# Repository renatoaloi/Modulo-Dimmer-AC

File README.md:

# Modulo-Dimmer-AC
Arquivos do EAGLE CAD do Módulo Dimmer AC REV3, incluindo GERBERs para fabricação

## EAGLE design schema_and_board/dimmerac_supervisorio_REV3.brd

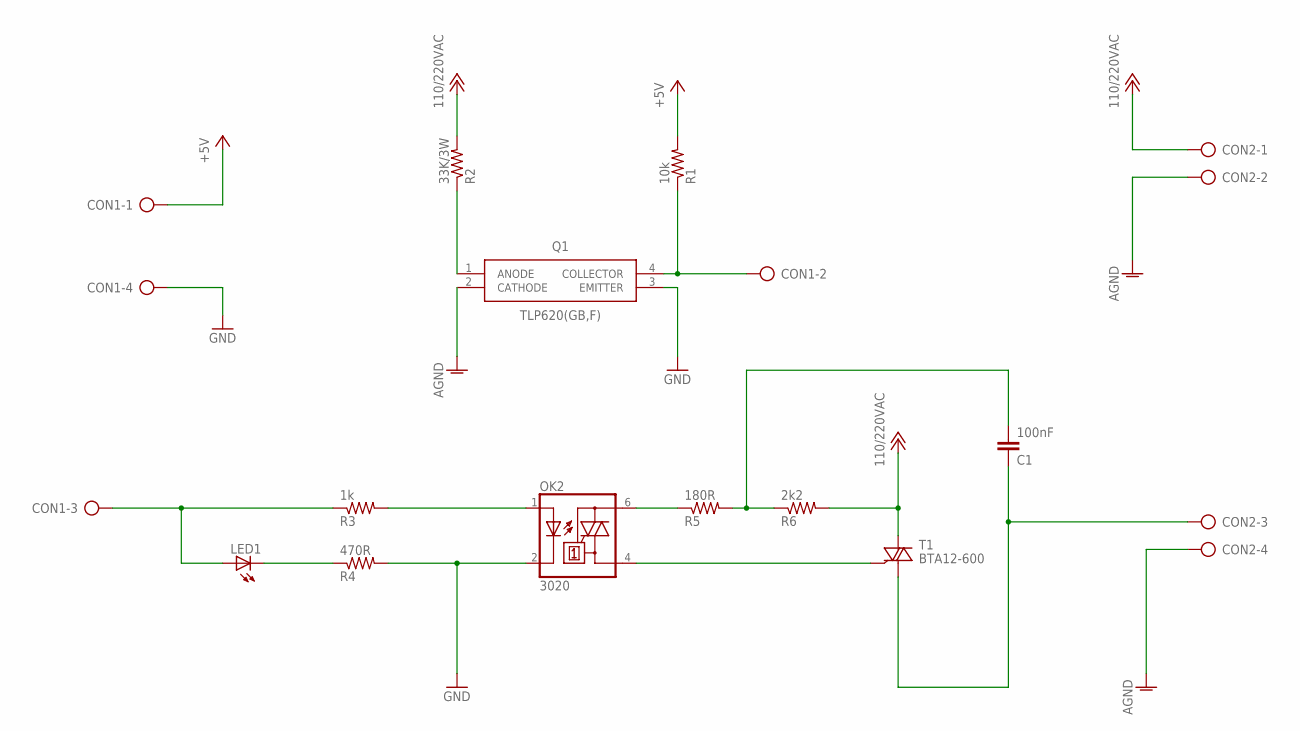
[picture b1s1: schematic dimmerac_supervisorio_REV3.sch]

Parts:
C1: 100nF; C15B7
CON1, CON2: AK500/4
LED1: LED5MM
OK2: 3020; DIL06
Q1: TLP620(GB,F); DIP762W60P254L448H380Q4N
R1: 10k; AXIAL-0.3
R2: 33K/3W; AXIAL-0.6
R3: 1k; AXIAL-0.3
R4: 470R; AXIAL-0.3
R5: 180R; AXIAL-0.3
R6: 2k2; AXIAL-0.3
T1: BTA12-600; TO220BH

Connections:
+5V: CON1.1, R1.P$2 (2)
+12V: CON2.1, R2.P$2 (2), R6.P$2 (2), T1.T2 (A2)
AGND: CON2.2, CON2.4, Q1.2 (CATHODE)
GND: CON1.4, OK2.2 (C), Q1.3 (EMITTER), R4.P$2 (2)
unnamed: CON1.2, Q1.4 (COLLECTOR), R1.P$1 (1)
unnamed: Q1.1 (ANODE), R2.P$1 (1)
unnamed: OK2.1 (A), R3.P$2 (2)
unnamed: LED1.K (C), R4.P$1 (1)
unnamed: CON1.3, LED1.A, R3.P$1 (1)
unnamed: OK2.4 (A1), T1.G
unnamed: OK2.6 (A2), R5.P$1 (1)
unnamed: C1.2, R5.P$2 (2), R6.P$1 (1)
unnamed: C1.1, CON2.3, T1.T1 (A1)

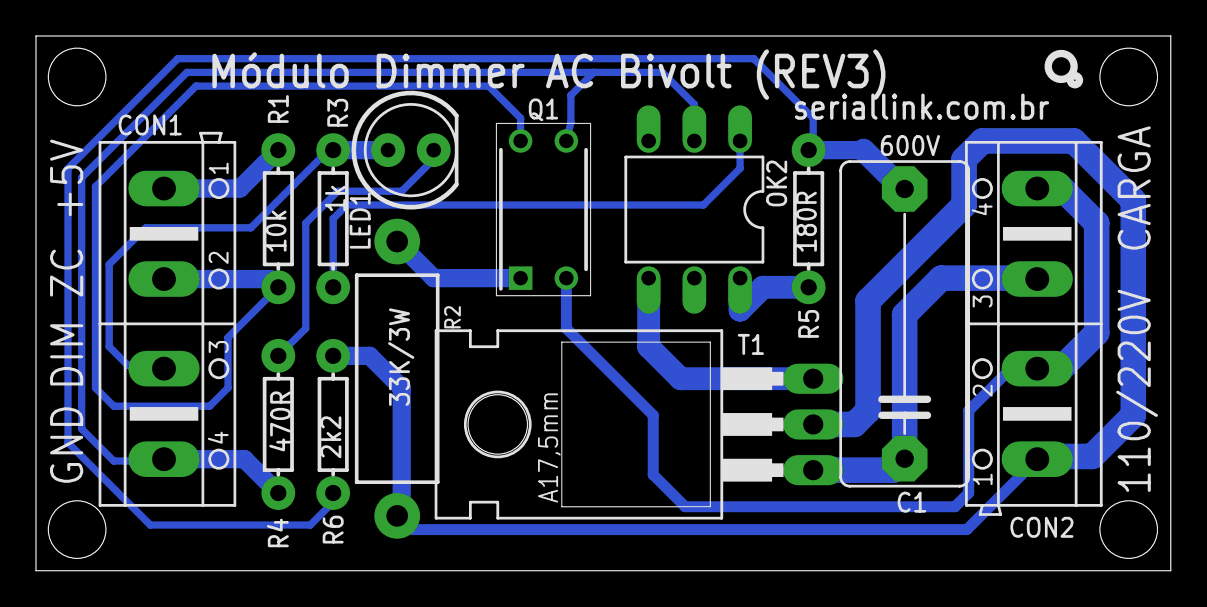
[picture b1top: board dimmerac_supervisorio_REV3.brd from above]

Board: 2 copper layers, 63.0 x 29.7 mm, 13 parts (0 on the bottom side), 13 nets.

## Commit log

2017-10-30 Incluindo arquivos BRD, SCH e GERBER
2017-10-30 atualizando arquivos

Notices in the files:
parts and their libraries:
SparkFun-LED: Licensing: CC v3.0 Share-Alike You are welcome to use this library for commercial purposes.
